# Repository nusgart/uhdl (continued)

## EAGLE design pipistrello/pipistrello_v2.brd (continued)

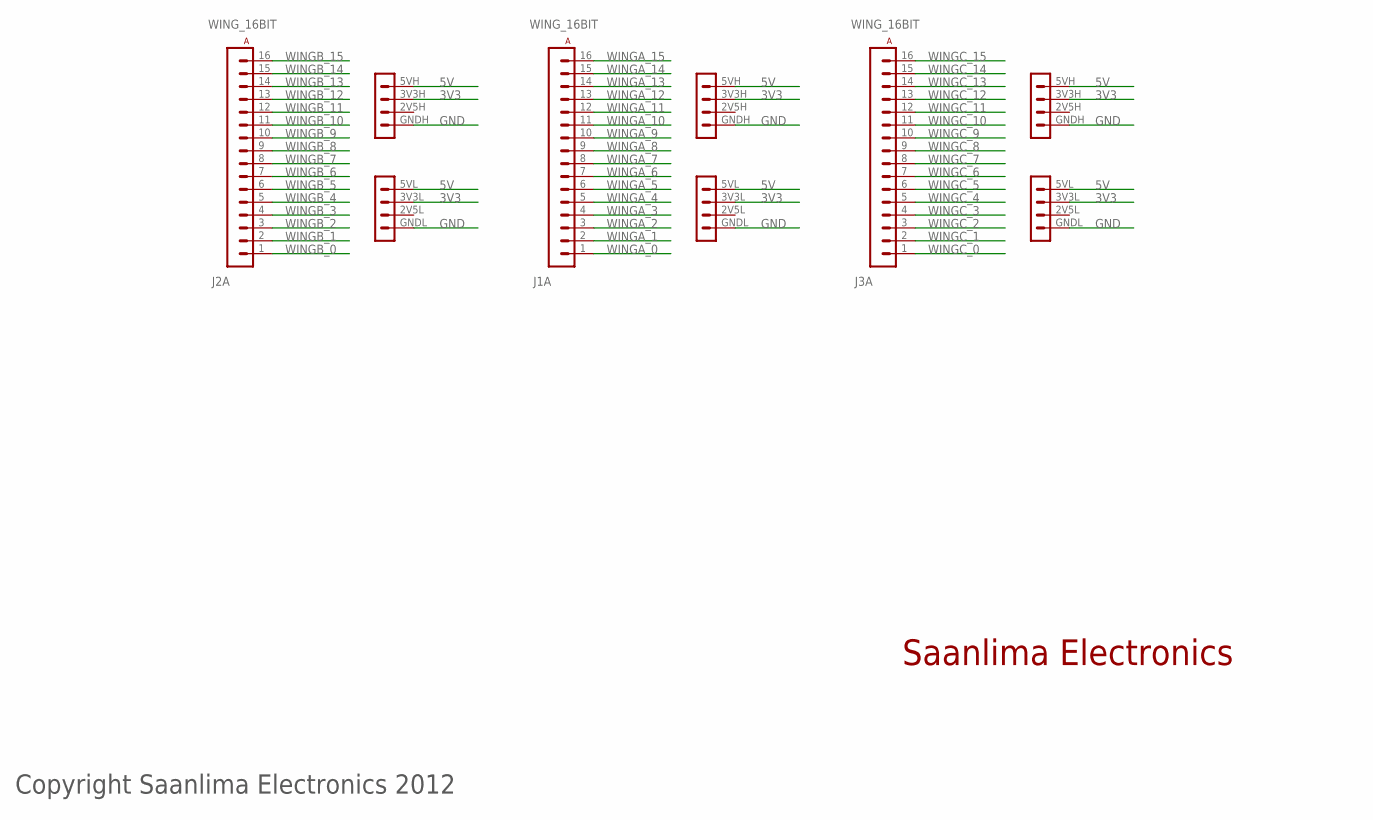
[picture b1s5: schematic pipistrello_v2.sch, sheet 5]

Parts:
J1, J2, J3: WING_16BIT

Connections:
3V3: J1.3V3H (3V3), J1.3V3L (3V3), J2.3V3H (3V3), J2.3V3L (3V3), J3.3V3H (3V3), J3.3V3L (3V3); also elsewhere on the board
5V: J1.5VH (5V), J1.5VL (5V), J2.5VH (5V), J2.5VL (5V), J3.5VH (5V), J3.5VL (5V); also elsewhere on the board
GND: J1.GNDH (GND), J1.GNDL (GND), J2.GNDH (GND), J2.GNDL (GND), J3.GNDH (GND), J3.GNDL (GND); also elsewhere on the board
WINGA_0: J1.1 (A1); also elsewhere on the board
WINGA_1: J1.2 (A2); also elsewhere on the board
WINGA_2: J1.3 (A3); also elsewhere on the board
WINGA_3: J1.4 (A4); also elsewhere on the board
WINGA_4: J1.5 (A5); also elsewhere on the board
WINGA_5: J1.6 (A6); also elsewhere on the board
WINGA_6: J1.7 (A7); also elsewhere on the board
WINGA_7: J1.8 (A8); also elsewhere on the board
WINGA_8: J1.9 (A9); also elsewhere on the board
WINGA_9: J1.10 (A10); also elsewhere on the board
WINGA_10: J1.11 (A11); also elsewhere on the board
WINGA_11: J1.12 (A12); also elsewhere on the board
WINGA_12: J1.13 (A13); also elsewhere on the board
WINGA_13: J1.14 (A14); also elsewhere on the board
WINGA_14: J1.15 (A15); also elsewhere on the board
WINGA_15: J1.16 (A16); also elsewhere on the board
WINGB_0: J2.1 (A1); also elsewhere on the board
WINGB_1: J2.2 (A2); also elsewhere on the board
WINGB_2: J2.3 (A3); also elsewhere on the board
WINGB_3: J2.4 (A4); also elsewhere on the board
WINGB_4: J2.5 (A5); also elsewhere on the board
WINGB_5: J2.6 (A6); also elsewhere on the board
WINGB_6: J2.7 (A7); also elsewhere on the board
WINGB_7: J2.8 (A8); also elsewhere on the board
WINGB_8: J2.9 (A9); also elsewhere on the board
WINGB_9: J2.10 (A10); also elsewhere on the board
WINGB_10: J2.11 (A11); also elsewhere on the board
WINGB_11: J2.12 (A12); also elsewhere on the board
WINGB_12: J2.13 (A13); also elsewhere on the board
WINGB_13: J2.14 (A14); also elsewhere on the board
WINGB_14: J2.15 (A15); also elsewhere on the board
WINGB_15: J2.16 (A16); also elsewhere on the board
WINGC_0: J3.1 (A1); also elsewhere on the board
WINGC_1: J3.2 (A2); also elsewhere on the board
WINGC_2: J3.3 (A3); also elsewhere on the board
WINGC_3: J3.4 (A4); also elsewhere on the board
WINGC_4: J3.5 (A5); also elsewhere on the board
WINGC_5: J3.6 (A6); also elsewhere on the board
WINGC_6: J3.7 (A7); also elsewhere on the board
WINGC_7: J3.8 (A8); also elsewhere on the board
WINGC_8: J3.9 (A9); also elsewhere on the board
WINGC_9: J3.10 (A10); also elsewhere on the board
WINGC_10: J3.11 (A11); also elsewhere on the board
WINGC_11: J3.12 (A12); also elsewhere on the board
WINGC_12: J3.13 (A13); also elsewhere on the board
WINGC_13: J3.14 (A14); also elsewhere on the board
WINGC_14: J3.15 (A15); also elsewhere on the board
WINGC_15: J3.16 (A16); also elsewhere on the board

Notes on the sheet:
Copyright Saanlima Electronics 2012
Saanlima Electronics

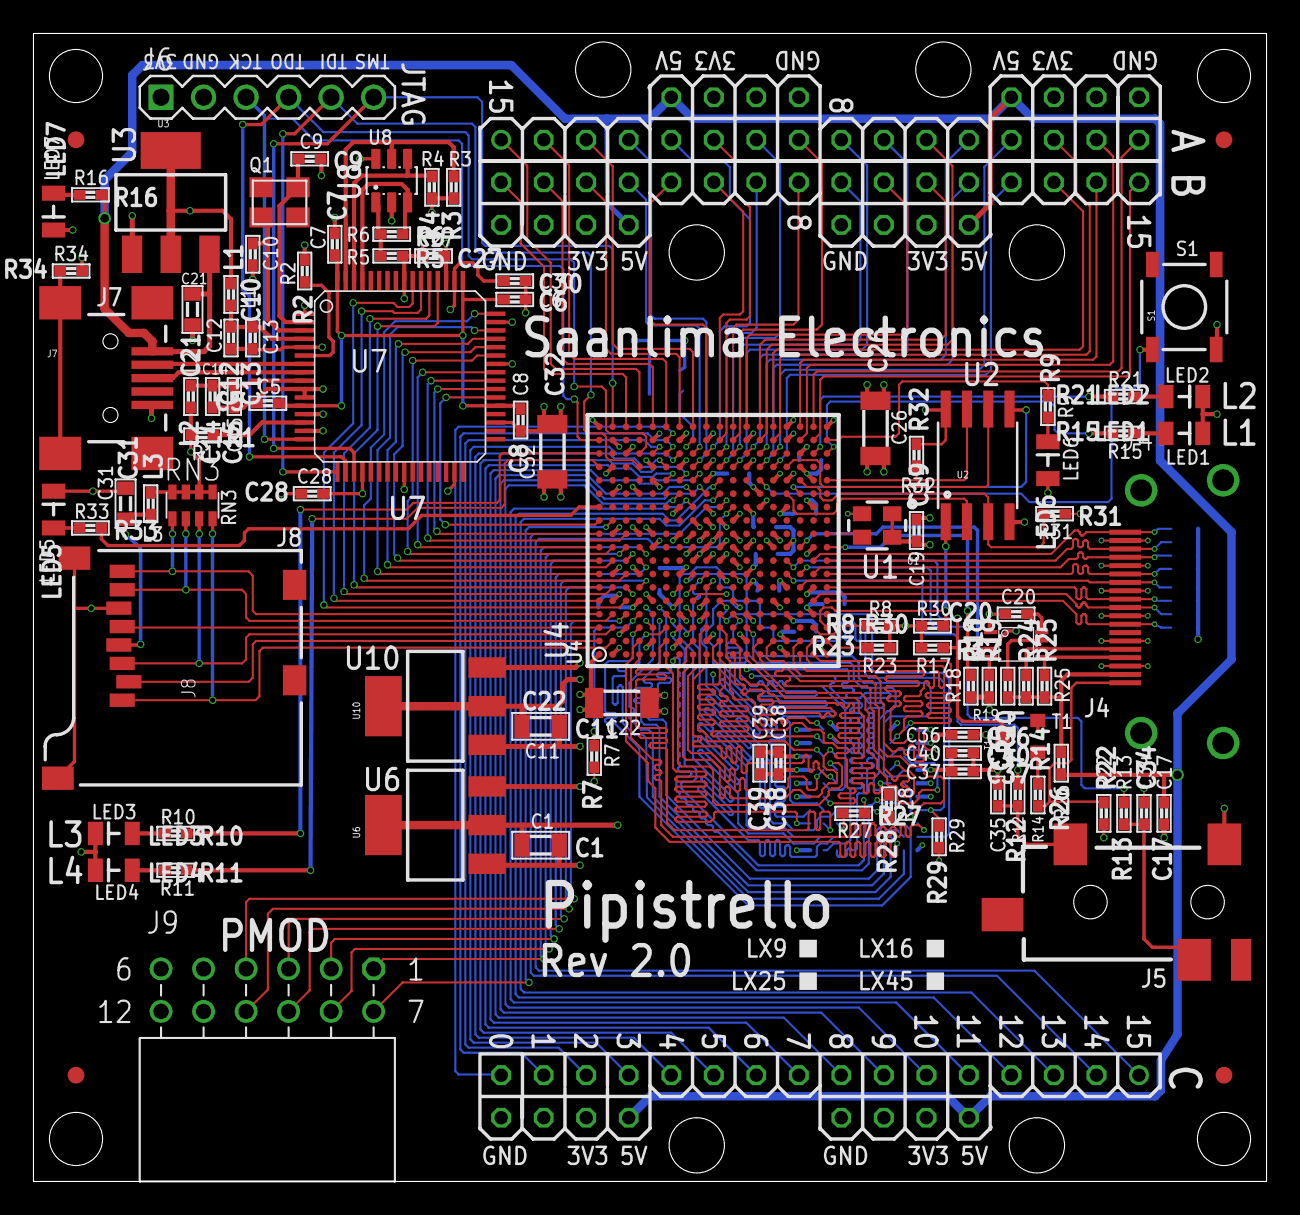
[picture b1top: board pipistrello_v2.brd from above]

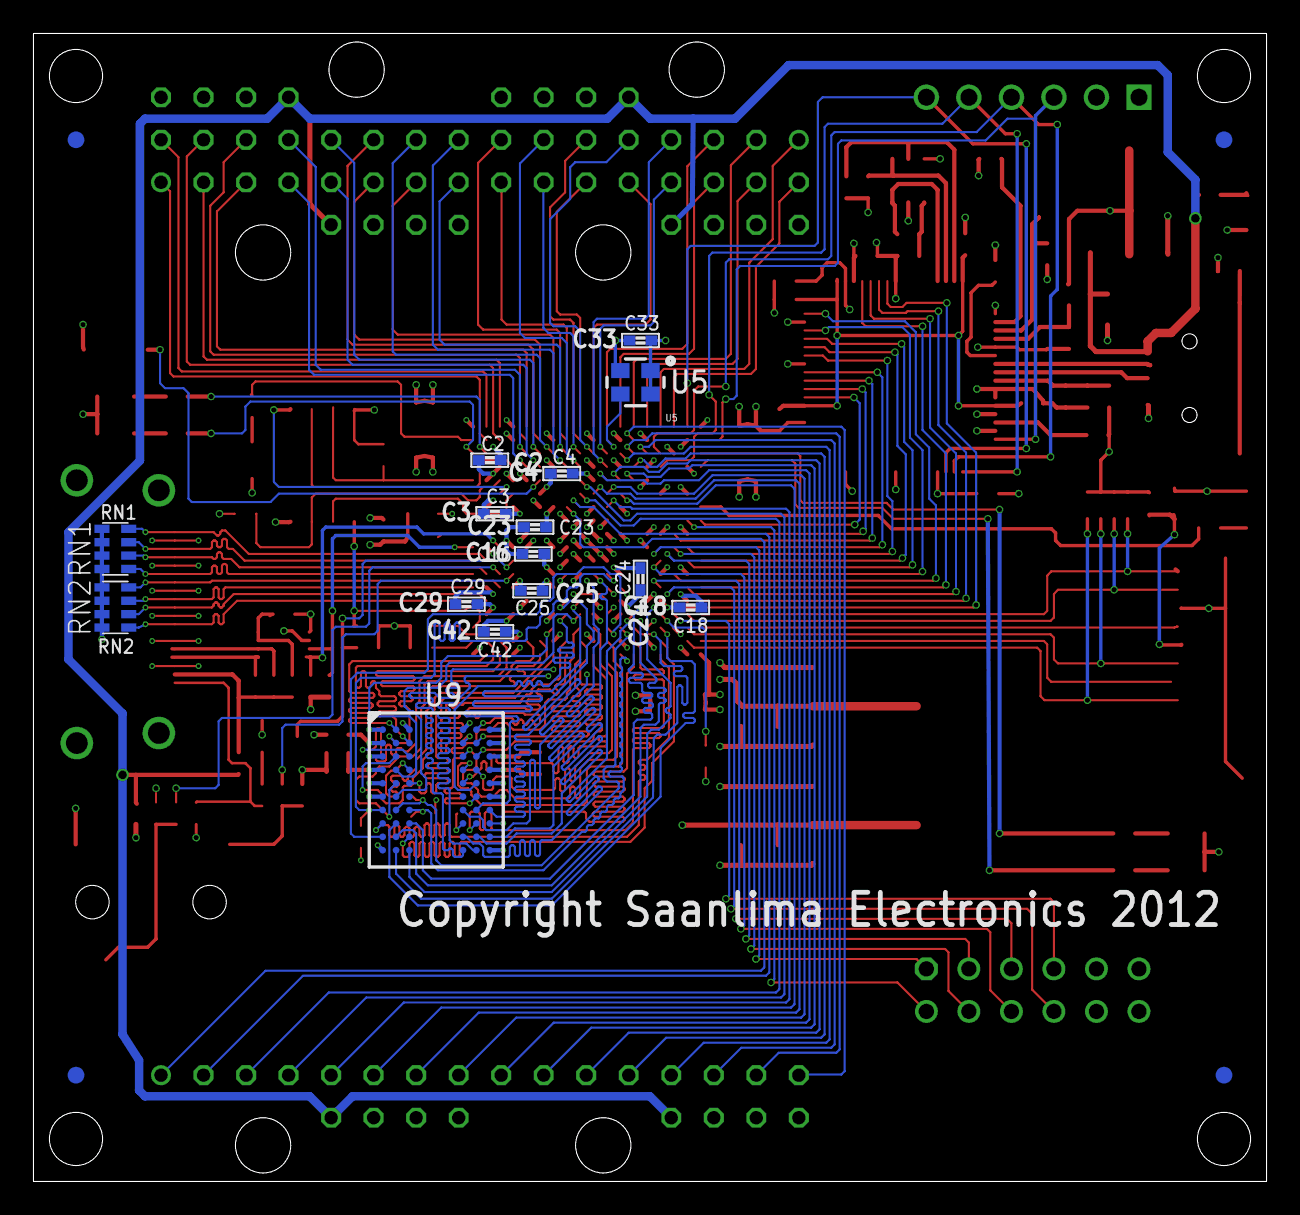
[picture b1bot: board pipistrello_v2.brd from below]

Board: 4 copper layers, 73.7 x 68.6 mm, 119 parts (19 on the bottom side), 187 nets.

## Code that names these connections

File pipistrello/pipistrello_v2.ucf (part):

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# SPI Flash
#NET "flash_miso"     LOC = "R13"  | IOSTANDARD = LVTTL | DRIVE = 8 | SLEW = FAST | PULLUP ; 
#NET "flash_mosi"     LOC = "T13"  | IOSTANDARD = LVTTL | DRIVE = 8 | SLEW = FAST ; 
#NET "flash_cs"       LOC = "V3"   | IOSTANDARD = LVTTL | DRIVE = 8 | SLEW = FAST | PULLUP  ; 
#NET "flash_sck"      LOC = "R15"  | IOSTANDARD = LVTTL | DRIVE = 8 | SLEW = FAST ;
#NET "flash_wp"       LOC = "T14"  | IOSTANDARD = LVTTL | DRIVE = 8 | SLEW = FAST | PULLUP ;
#NET "flash_hold"     LOC = "V14"  | IOSTANDARD = LVTTL | DRIVE = 8 | SLEW = FAST | PULLUP ;

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#NET "edid_sda"       LOC = "T9"   | IOSTANDARD = I2C ;
#NET "edid_scl"       LOC = "V9"   | IOSTANDARD = I2C ;

#NET "hdmi_det"       LOC = "R8"   | IOSTANDARD = LVTTL ;

# audio
#NET "audio_l"        LOC = "R7"   | IOSTANDARD = LVTTL | SLEW = SLOW | DRIVE = 8 ;
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#NET "sd_sck"         LOC = "A3"   | IOSTANDARD = SDIO | SLEW = FAST | DRIVE = 8 ;

# leds
#NET "LED1"           LOC = "V16"  | IOSTANDARD = LVTTL | SLEW = SLOW | DRIVE = 8 ;
#NET "LED2"           LOC = "U16"  | IOSTANDARD = LVTTL | SLEW = SLOW | DRIVE = 8 ;
#NET "LED3"           LOC = "A16"  | IOSTANDARD = LVTTL | SLEW = SLOW | DRIVE = 8 ;
#NET "LED4"           LOC = "A15"  | IOSTANDARD = LVTTL | SLEW = SLOW | DRIVE = 8 ;
#NET "LED5"           LOC = "A12"  | IOSTANDARD = LVTTL | SLEW = SLOW | DRIVE = 8 ;

# switch
#NET "switch"         LOC = "N14"  | IOSTANDARD = LVTTL | PULLDOWN ;

# PMOD
#NET "PMOD1_IO1"      LOC = "D9"   | IOSTANDARD = LVTTL | SLEW = SLOW | DRIVE = 8 ;
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
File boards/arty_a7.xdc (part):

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#set_property CLOCK_DEDICATED_ROUTE FALSE [get_nets sysclk]

## Switches
set_property -dict { PACKAGE_PIN A8    IOSTANDARD LVCMOS33 } [get_ports { switch[0] }]; #IO_L12N_T1_MRCC_16 Sch=sw[0]
set_property -dict { PACKAGE_PIN C11   IOSTANDARD LVCMOS33 } [get_ports { switch[1] }]; #IO_L13P_T2_MRCC_16 Sch=sw[1]
set_property -dict { PACKAGE_PIN C10   IOSTANDARD LVCMOS33 } [get_ports { switch[2] }]; #IO_L13N_T2_MRCC_16 Sch=sw[2]
set_property -dict { PACKAGE_PIN A10   IOSTANDARD LVCMOS33 } [get_ports { switch[3] }]; #IO_L14P_T2_SRCC_16 Sch=sw[3]

## RGB LEDs
set_property -dict { PACKAGE_PIN E1    IOSTANDARD LVCMOS33 } [get_ports { led[4] }]; #IO_L18N_T2_35 Sch=led0_b
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set_property -dict { PACKAGE_PIN B11   IOSTANDARD LVCMOS33 } [get_ports { mmc_do }]; #IO_L4P_T0_15 Sch=ja[2]		# MOSI
set_property -dict { PACKAGE_PIN A11   IOSTANDARD LVCMOS33 } [get_ports { mmc_di }]; #IO_L4N_T0_15 Sch=ja[3]		# MISO
set_property -dict { PACKAGE_PIN D12   IOSTANDARD LVCMOS33 } [get_ports { mmc_sclk }]; #IO_L6P_T0_15 Sch=ja[4]		# SCK
#set_property -dict { PACKAGE_PIN D13   IOSTANDARD LVCMOS33 } [get_ports { ja[4] }]; #IO_L6N_T0_VREF_15 Sch=ja[7]	# DAT1
#set_property -dict { PACKAGE_PIN B18   IOSTANDARD LVCMOS33 } [get_ports { ja[5] }]; #IO_L10P_T1_AD11P_15 Sch=ja[8]	# DAT2
#set_property -dict { PACKAGE_PIN A18   IOSTANDARD LVCMOS33 } [get_ports { ja[6] }]; #IO_L10N_T1_AD11N_15 Sch=ja[9]	# CD
#set_property -dict { PACKAGE_PIN K16   IOSTANDARD LVCMOS33 } [get_ports { ja[7] }]; #IO_25_15 Sch=ja[10]

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
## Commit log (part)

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2017-12-08 Fix pathnames to point properly.
2017-12-08 pli: Compile on 64-bit.
2017-12-08 niox/verif/mmc_model.v: Fix typo.
2017-12-08 pipistrello/pipistrello_v2.01.ucf: Restore to original.
2017-12-08 pipistrello/pipistrello_v2.01.ucf: Restore for CADR usage.
2017-12-08 NOTES.txt: Update.
2017-12-08 pipistrello/pipistrello_v2.03.ucf: Minor cleanup, document wing layout.
2017-12-08 pipistrello/pipistrello_v2.03.ucf: Fix typo.
2017-12-08 lisp/cc.c: Random minor fixups.
2017-12-08 Use new UCF file for Pipistrello + Arcadewing.
2017-12-08 Switch on chipscope for mmc debug, and disable for cpu.
2017-12-08 verif/run-mmc.v: Fix from Brad.
2017-12-08 niox/verif/mmc_model.v: Disable USE_FILE.
2017-12-08 NOTES-ams.text: New file.
2017-12-08 NOTES-ams.text: Update.
2017-12-08 rtl/mmc_block_dev.v: Mental note about order of bits.
2017-12-08 rtl/mmc.v: Mental order about bits.
2017-12-08 NOTES.txt: Fix typo.
2017-12-08 niox: Update NIOX location.
2017-12-08 niox/rtl/top_niox.v: Update top level to use new UCF file (Pipistrello, and Arcade MegaWing).
2017-12-08 rtl/mmc_block_dev.v: Revert non-connected lines to low.
2017-12-08 niox/verif/run.vc: Adjust file names for NIOX softcore.
2017-12-08 niox: Fix to match cadr top-level.
2017-12-08 Remove generated files.
2017-12-08 niox_defines.v: Add dummy file.
2017-12-08 niox: Update project files.
2017-12-08 ise-lx45/top.xst: Add file.
2017-12-08 niox, ise-lx45: Update project files.
2017-12-08 Add needed directory, and remove old isim config.
2017-12-08 ./top_niox.ut: New file.
2017-12-08 Add UT file.
2017-12-08 Changes from Brad.
2017-12-08 More changes from Brad.
2017-12-08 niox: Revert bits so that things build.
2017-12-08 rtl/mmc_wrapper.v: New (dummy) file.
2017-12-08 Match NIOX.
2017-12-08 rtl/top_lx45.v: Revert to Brad's version.
2017-12-08 README.md -> README: Rename.
2017-12-08 NOTES-ams.text: Merge with NOTES.txt.
2017-12-08 Remove spy_mmc code; was not doing anything anyway.
2017-12-08 rtl/caddr.v: Checkpoint.
2017-12-08 rtl/caddr.v: Checkpoint (works).
2017-12-08 Checkpoint ...
2017-12-08 Checkpoint.
2017-12-08 rtl/cadr: Indent code.
2017-12-08 cadr: Checkpoint.
2017-12-08 Checkpooint.
2017-12-08 cadr: Modularize code.
2017-12-08 caddr.v: Revert parts of previous commit.
2017-12-08 Adjust module instances.
2017-12-08 Clean up.
2017-12-08 Reorganize.
2017-12-08 rtl/caddr.v: Fixup.
2017-12-08 Checkpoint (busint extracted into top).
2017-12-08 Checkpoint; after modularization is done.
2017-12-08 Update project files.
2017-12-08 rtl/caddr.v: Minor space fixes.
2017-12-08 Minor wire clean up.
2017-12-08 Wire cleanup.
2017-12-08 cadr: Collapse some input and output ports.
2017-12-08 Revert [2716] and [2715].
2017-12-08 cadr: Order cpu state arguments.
2017-12-08 rtl/cadr/dspctl.v: More wire to top.
2017-12-08 spy0: Clean up.
2017-12-08 vhdl: Start of VHDLification.
2017-12-08 Cleanup.
2017-12-08 Get ISim working again.
2017-12-08 Cleanups.
2017-12-08 Convert DOS EOL:ed files to UNIX.
2017-12-08 NOTES.txt: Cleanup.
2017-12-08 NOTEX.txt: Updated.
2017-12-08 NOTES.txt -> NOTES: Rename file.
2017-12-08 ipcore_ise13: Delete directory.
2017-12-08 ipcore_ise14.5: Delete directory.
2017-12-08 Reorganize project and nuke old files.
2017-12-08 Regenerate IP Cores.
2017-12-08 Split ROMs out into seperate files.
2017-12-08 Rename boot prom source file to match module name.
2017-12-08 Rename files to match module name, move testbenches and top levels to tb/.
2017-12-08 rtl/xbus_unibus.v: Fix duplicate input from previous commit.
2017-12-08 Remove `include directives, no need for them due to global include of rtl/defines.vh.
2017-12-08 Remove usage of DBG_DLY.
2017-12-08 rtl/vga_display.v: Remove unused code.
2017-12-08 rtl: Minor cleanups.
2017-12-08 rtl/cadr/spc.v: Reorganize and remove unused code.
2017-12-08 mmc_block_dev.v: Remove __CVER__ ifdef.
2017-12-08 mmc.v: Remove __CVER__ ifdef.
2017-12-08 caddr.v: Remove __CVER__ ifdef.
2017-12-08 rtl/mmc.v, rtl/mmc_block_dev.v: Seperate chipscope stuff with a comment.
2017-12-08 rtl: Clean up RAM/ROM modules.
2017-12-08 rtl/lx45_ram_controller.v: Add back synthesis attribute.
2017-12-08 rtl: Restore synthesis attributes, and some `define to keep things working.
2017-12-08 rtl/ps2_send.v: Remove useless ifdef.
2017-12-08 rtl/xbus_ram.v: Remove useless ifdef.
2017-12-08 xbus_disk.v: Remove useless ifdef.
2017-12-08 rtl/ps2_support.v: Cleanup.
2017-12-08 mouse.v: Minor cleanup.
2017-12-08 rtl/mmc_block_dev.v: Cleanup.
2017-12-08 rtl/keyboard.v: Cleanup.
2017-12-08 rtl: Fix file headers.
2017-12-08 rtl/cadr/amem01.v; Minor cleanup.
2017-12-08 rtl: Enable PLATCH code.
2017-12-08 lm-3.xise: Update project file.
2017-12-08 rtl: Minor clean up.
2017-12-08 rtl: Remove useless port in dpram modules.
2017-12-08 tb/run_spy.v: Removed unused ports to spy_port.
2017-12-08 rtl: Move LX45 LPDDR defines to defines.vh.
2017-12-08 part_16kx49ram.v: Only define q_a as a reg when simulating.
2017-12-08 rtl/defines.vh: Further cleanup.
2017-12-08 defines.vh: Whitespace cleanup.
2017-12-08 Update project file.
2017-12-08 cold.text: New file.
2017-12-08 cold.text: Update.
2017-12-08 Rename project files.
2017-12-08 Regenerate cores (basically just updates the timestamp).
2017-12-08 uhdl: Rename test benches to something more descriptive. Update project files.
2017-12-09 README: Update.
2018-02-16 created null memory controller
2018-02-17 more fuckery for vivado
2018-02-17 changed to xilinx ram primitives
2018-02-17 add include for defines because vivado can't do global headers with custom IP block packaging
2018-02-24 NIOX: Add submodule for NIOS-II clone core.
2019-05-30 Initial conversion to Vivado and Artix-7
2019-05-30 Change verilog syntax to conform to SystemVerilog standard
    Vivado requires type declaration on inputs and outputs when using
    default_nettype none
2019-06-07 Properly seperate A7 support from the LX45 and further work on DDR3 iface
    I've generated a new DDR3 ip using the files provided for the Arty-A7-35T, which
    is the target board for this port. Additionally, I have redone the top level
    pins to match the DDR3 interface (lots of renames, a few addtions and removals).
    The design still is not completely routed, but it is much closer -- only two
    circuits are unroutable. I will continue investigating this.
2019-06-07 Project generates bitstream.
    Turns out only an additional constraint was needed to fix things.
2019-06-18 Fix clock frequency, improve timing, and seperate VGA/DDR clock generation.
    Some paths still have negative slack, but the bitstream will generate.
    More importantly, I have told Vivado the Arty A7 runs at 100 MHz, which is
    what led me to notice the above issues. Prior to this, Vivado seemed to think
    that the design would run at some ridiculously high frequency. It thus computed
    that the design would consume 60 watts (the A7 supplies around 5.2 W to the FPGA
    at most), which told me that I had forgotten to set the sysclk frequency.
2019-07-21 DDR now works: disable some inferred block rams to allow full usage of VRAM.
2019-08-22 Further work on Arty A7: memory controller and SD controller
    The memory controller has been rewritten for correctness, which includes
    using its output as the main system clock, which is annoying, since no DDR
    frequency achievable by the XC7A35T can be cleanly divided to 50 MHz. In
    the long run, I will just use multiple clocks, but for now, using the 81.25 MHz
    clock provided reduces timing problems.
    Also, I have started implementing SDHC/SDXC support.
2019-08-23 Fix SDHC initialization, I think.
    Sadly it's not easy to tell until the entire thing boots because I don't have
    a simulation model of an SDHC card, but it does appear to get all the way to
    the idle state. The problem is that it seems to either stay there, or it
    could be that the VGA display doesn't actually work.
2019-09-20 Add LED controller for debugging, and try to fix SDHC and timing.
    The LED controller permits me to make much more effective use of the Arty's
    LEDs, including moded operation (different switch settings --> different
    meanings for each LED).
    The largest timing fix was to introduce a synchronizer for the global reset,
    which vastly improved timing. Most of the remaining "error" is on the other
    reset lines, but it's not neccessary to "fix" them (I did it to reduce the
2020-04-23 Fix sd_hc to not be a latch.
2020-04-23 Disable VGA debug white-lines feature.
2020-04-23 Increase board-state LED size (allows for more data to be seen).
2020-04-23 Implement a new SD controller using LJW2030's SDHC controller
    LWJ2030's module natively supports SDHC so it might work better.
2020-08-27 Disable RAM inference -- makes PNR take longer for some reason
2020-08-27 Fix ram controller
2020-08-27 Add location counter to LED "display"
2020-08-27 Change VGA mode information
2020-08-27 Small changes to xbus_ram
2021-03-05 Fix spy port, CC now works.
    There were two problems: TX and RX were swapped, and spy_port never set its
    response data. Both problems are fixed by this commit.
2021-05-12 Add missing files
2021-05-12 .gitignore: Don't ignore *.prj files; needed for MIG.
2021-05-12 .gitignore: Don't ignore files starting with "uhdl".
2021-05-12 Move shared cores to cores/.
2021-05-12 Move files under cadr.srcs/sources_1/new to top-level.
2021-05-12 Move files under cadr.srcs/sim_1/new to top-level.
2021-05-12 Replace ram_controller_A7 with memory_controller_A7.
2021-05-12 Rename .version to build_id.vh.
2021-05-12 Rename and update top-level files and test benches to match Tumbleweed.
2021-05-12 GNUmakefile: Update from Tumbleweed.
2021-05-12 CADR4/MSKG4.v: Move mask ROMs.
2021-05-12 GNUmakefile: Make so you can run this without hdlmake.mk.
2021-05-12 README -> README.md: Rename.
2021-05-12 CADR4/IRAML/PROM.v: Move boot PROM.
2021-05-12 keyboard.v: Update from Tumbleweed
2021-05-12 busint.v: Update from Tumbleweed.
2021-05-12 support_tb.v: Update from Tumbleweed.
2021-05-12 mouse.v, mouse_tb.v: Update from Tumbleweed.
2021-05-12 CADR4: Sync with Tumbleweed changes.
    Converts module declerations to Verilog-2001.
2021-05-12 template.v: Add file.
2021-05-12 uhdl_pipistrello.v, uhdl_pipistrello_tb.v: Restore files; and update from Tumbleweed.
2021-05-12 block_dev_mmc.v: Update from Tumbleweed; Verilog-2001.
2021-05-12 uhdl_sim.cpp: Update from Tumbleweed.
2021-05-12 Remove Chaosnet support.
2021-05-12 ps2_support.v: Update from Tumbleweed.
2021-05-12 ram_controller_tb.v: Update from Tumbleweed.
2021-05-12 csr.c: Delete file.
2021-05-12 TODO: Add file.
2021-05-12 cadr.mk: Update from Tumbleweed.
2021-05-12 CADR4.netlist, CADR4.wires: Add files.
2021-05-12 scancode_convert.v, scancode_convert_tb.v: Update from Tumbleweed.
2021-05-12 xbus_disk.v: Update from Tumbleweed.
2021-05-12 cores/hz60.v: Update from Tumbleweed.
2021-05-12 uhdl.v: Update from Tumbleweed.
2021-05-12 cores/us.v: Update from Tumbleweed.
2021-05-12 xbus_tv.v: Update from Tumbleweed.
2021-05-12 uhdl_common.v: Update from Tumbleweed.
2021-05-12 cores/rom.v: Update from Tumbleweed.
2021-05-12 xbus_unibus.v: Update from Tumbleweed.
2021-05-12 cores/uart.v: Update from Tumbleweed.
2021-05-12 xbus_io.v: Update from Tumbleweed.
2021-05-12 cadr.xpr: Update project file with correct locations.
2021-05-12 boards/pipistrello.mk: Update from Tumbleweed.
2021-05-12 mmc.v, mmc_model.v, mmc_tb.v, mmc_wrapper.v: Update from Tumbleweed.
2021-05-12 xbus_spy.v: Update from Tumbleweed.
2021-05-12 cores/ic_74181.v, cores/ic_74182.v: Update from Tumbleweed.
2021-05-12 vga_display.v: Update to Verilog-2001 declerations.
2021-05-15 Set default board to Arty A7 and update gitignore
2021-05-18 Fix VGA display
2021-05-18 Update README with specific information about the Arty A7 port
2021-05-18 Get rid of the non-functional Artix-7 copy of the Spartan 6 MIG IP.
    This change does _not_ affect anything in the Pipistrello tree.
2021-05-21 Fix VGA horizontal counter overflow
    The problem was that the horizontal counter was eleven bits but a 1080p line is
    2200 pixels wide, so the horizontal counter overflowed. Both the horizontal and
    vertical counters are thirteen bits now, which should allow resolutions up to
    8192x8192, which is probably more than VGA can reasonably support.
2021-05-22 Minor fixes and tweaks
